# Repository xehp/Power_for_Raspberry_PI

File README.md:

# Power_for_Raspberry_PI
An UPS and some extras for using a Raspberry PI as web interface GUI in an embedded system.

The UPS and HAT selected need to match

RPi_HAT_isolated_rs232 and SuperCapUps10_rs232 are matching.

Copyright (C) 2021
Henrik Björkman
www.eit.se/hb

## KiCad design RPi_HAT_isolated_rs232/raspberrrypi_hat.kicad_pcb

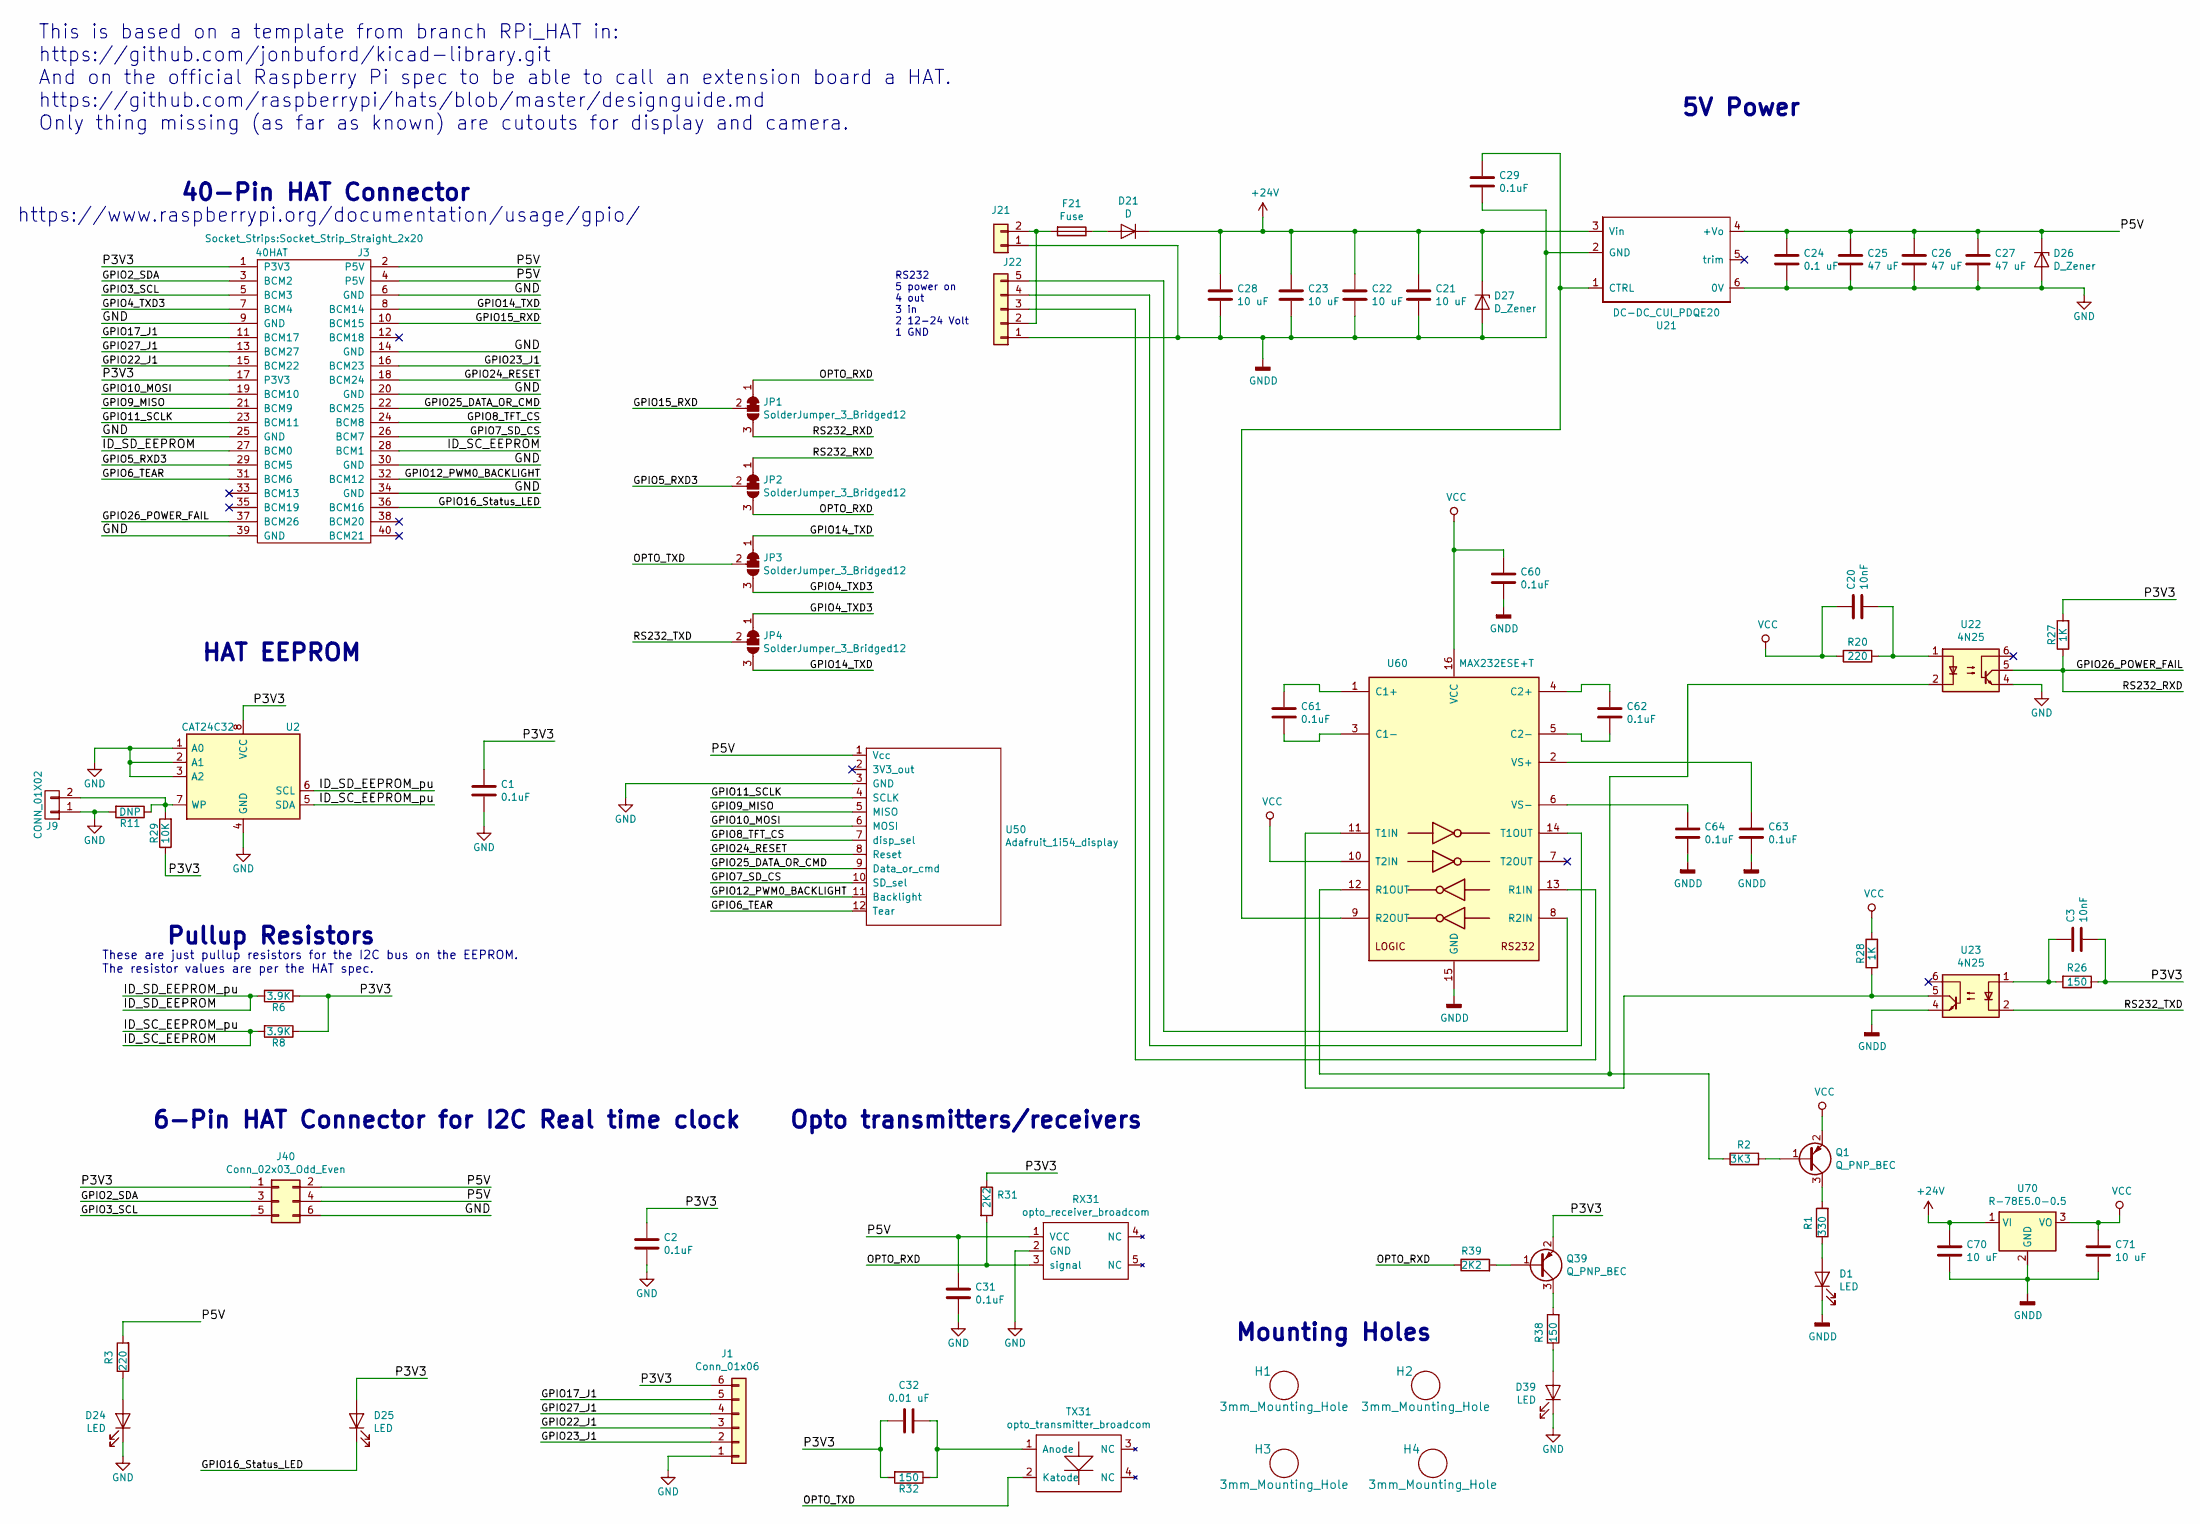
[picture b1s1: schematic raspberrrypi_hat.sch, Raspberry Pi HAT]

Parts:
C1, C2, C31, C60, C61, C62, C63, C64: 0.1uF; C_0805_2012Metric
C3, C20: 10nF; C_0805_2012Metric
C21, C22, C23, C28, C70, C71: 10 uF; C_1206_3216Metric
C24: 0.1 uF; C_0805_2012Metric
C25, C26, C27: 47 uF; C_1206_3216Metric
C29: 0.1uF; C_0805_2012Metric_Pad1.15x1.40mm_HandSolder
C32: 0.01 uF; C_0805_2012Metric
D1, D24, D39: LED; LED_0805_2012Metric
D21: D; D_SMA
D25: LED; LED_D3.0mm
D26: D_Zener; D_SMB
D27: D_Zener; D_A-405_P2.54mm_Vertical_AnodeUp
F21: Fuse; R_Radial_Power_L11.0mm_W7.0mm_P5.00mm
H1, H2, H3, H4: 3mm_Mounting_Hole; NPTH_3mm_ID
J1: Conn_01x06; Molex_KK-254_AE-6410-06A_1x06_P2.54mm_Vertical
J3: 40HAT; Socket_Strip_Straight_2x20
J9: CONN_01X02; PinHeader_1x02_P2.54mm_Vertical
J21: Conn_01x02; connector_TE_Connectivity_2_pin
J22: Conn_01x05; Molex_KK-254_AE-6410-05A_1x05_P2.54mm_Vertical
J40: Conn_02x03_Odd_Even; PinHeader_2x03_P2.54mm_Vertical
JP1, JP2, JP3, JP4: SolderJumper_3_Bridged12; SolderJumper-3_P2.0mm_Open_TrianglePad1.0x1.5mm_NumberLabels
Q1, Q39: Q_PNP_BEC; SOT-23
R1: 330; R_0805_2012Metric_Pad1.15x1.40mm_HandSolder
R2: 3K3; R_0805_2012Metric_Pad1.15x1.40mm_HandSolder
R3: 220; R_0805_2012Metric_Pad1.15x1.40mm_HandSolder
R6, R8: 3.9K; R_0805_2012Metric_Pad1.15x1.40mm_HandSolder; MPN RC0402JR-0722RL
R11: DNP; R_0805_HandSoldering; MPN RC0402JR-0722RL
R20: 220; R_1206_3216Metric; MPN RC0402JR-0722RL
R26: 150; R_0805_2012Metric; MPN RC0402JR-0722RL
R27, R28: 1K; R_0805_2012Metric; MPN RC0402JR-0722RL
R29: 10K; R_0805_2012Metric; MPN RC0402JR-0722RL
R31, R39: 2K2; R_0805_2012Metric_Pad1.15x1.40mm_HandSolder
R32: 150; R_0805_2012Metric_Pad1.15x1.40mm_HandSolder; MPN RC0402JR-0722RL
R38: 150; R_0805_2012Metric_Pad1.15x1.40mm_HandSolder
RX31: opto_receiver_broadcom; opto_receiver_broadwell
TX31: opto_transmitter_broadcom; opto_transmitter_broadwell
U2: CAT24C32; SOIC-8_3.9x4.9mm_Pitch1.27mm
U21: DC-DC_CUI_PDQE20; DC-DC_CUI_PDQE20-D
U22, U23: 4N25; DIP-6_W7.62mm
U50: Adafruit_1i54_display
U60: MAX232ESE+T; SOIC-16_3.9x9.9mm_P1.27mm
U70: R-78E5.0-0.5; DC-DC-Recom-R78

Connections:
+24V: C21.1, C22.1, C23.1, C28.1, C70.1, D21.1 (K), D27.1 (K), U21.3 (Vin), U70.1 (VI)
/GPIO2_SDA: J3.3 (BCM2), J40.3
/GPIO3_SCL: J3.5 (BCM3), J40.5
/GPIO4_TXD3: J3.7 (BCM4), JP3.3 (B), JP4.1 (A)
/GPIO5_RXD3: J3.29 (BCM5), JP2.2 (C)
/GPIO7_SD_CS: J3.26 (BCM7), U50.10 (SD_sel)
/GPIO8_TFT_CS: J3.24 (BCM8), U50.7 (disp_sel)
/GPIO9_MISO: J3.21 (BCM9), U50.5 (MISO)
/GPIO10_MOSI: J3.19 (BCM10), U50.6 (MOSI)
/GPIO11_SCLK: J3.23 (BCM11), U50.4 (SCLK)
/GPIO12_PWM0_BACKLIGHT: J3.32 (BCM12), U50.11 (Backlight)
/GPIO14_TXD: J3.8 (BCM14), JP3.1 (A), JP4.3 (B)
/GPIO15_RXD: J3.10 (BCM15), JP1.2 (C)
/GPIO16_Status_LED: D25.1 (K), J3.36 (BCM16)
/GPIO17_J1: J1.5, J3.11 (BCM17)
/GPIO22_J1: J1.3, J3.15 (BCM22)
/GPIO23_J1: J1.2, J3.16 (BCM23)
/GPIO24_RESET: J3.18 (BCM24), U50.8 (Reset)
/GPIO25_DATA_OR_CMD: J3.22 (BCM25), U50.9 (Data_or_cmd)
/GPIO26_POWER_FAIL: J3.37 (BCM26), JP1.3 (B), JP2.1 (A), R27.1, U22.5
/GPIO27_J1: J1.4, J3.13 (BCM27)
/ID_SC_EEPROM: J3.28 (BCM1), R8.2, U2.5 (SDA)
/ID_SD_EEPROM: J3.27 (BCM0), R6.2, U2.6 (SCL)
/OPTO_RXD: JP1.1 (A), JP2.3 (B), R31.2, R39.1, RX31.3 (signal)
/OPTO_TXD: JP3.2 (C), TX31.2 (Katode)
/P3V3: C1.1, C2.1, C3.2, C32.2, D25.2 (A), J1.6, J3.1 (P3V3), J3.17 (P3V3), J40.1, Q39.2 (E), R6.1, R8.1, R26.1, R27.2, R29.1, R31.1, R32.2, U2.8 (VCC)
/P5V: C24.1, C25.1, C26.1, C27.1, C31.1, D26.1 (K), J3.2 (P5V), J3.4 (P5V), J40.2, J40.4, R3.2, RX31.1 (VCC), U21.4 (+Vo), U50.1 (Vcc)
/RS232_TXD: JP4.2 (C), U23.2
GND: C1.2, C2.2, C24.2, C25.2, C26.2, C27.2, C31.2, D24.1 (K), D26.2 (A), D39.1 (K), J1.1, J3.6 (GND), J3.9 (GND), J3.14 (GND), J3.20 (GND), J3.25 (GND), J3.30 (GND), J3.34 (GND), J3.39 (GND), J9.1, J40.6, R11.2, RX31.2 (GND), U2.1 (A0), U2.2 (A1), U2.3 (A2), U2.4 (GND), U21.6 (0V), U22.4, U50.3 (GND)
GNDD: C21.2, C22.2, C23.2, C28.2, C29.2, C60.2, C63.2, C64.2, C70.2, C71.2, D1.1 (K), D27.2 (A), J21.1, J22.1, U21.2 (GND), U23.4, U60.15 (GND), U70.2 (GND)
unnamed: C3.1, R26.2, U23.1
unnamed: C20.2, R20.1, U22.1
unnamed: C29.1, U21.1 (CTRL), U60.9 (R2OUT)
unnamed: C32.1, R32.1, TX31.1 (Anode)
unnamed: C61.1, U60.1 (C1+)
unnamed: C61.2, U60.3 (C1-)
unnamed: C62.1, U60.4 (C2+)
unnamed: C62.2, U60.5 (C2-)
unnamed: C63.1, U60.2 (VS+)
unnamed: C64.1, U60.6 (VS-)
unnamed: D1.2 (A), R1.1
unnamed: D21.2 (A), F21.1
unnamed: D24.2 (A), R3.1
unnamed: D39.2 (A), R38.1
unnamed: F21.2, J21.2, J22.2
unnamed: J9.2, R11.1, R29.2, U2.7 (WP)
unnamed: J22.3, U60.13 (R1IN)
unnamed: J22.4, U60.14 (T1OUT)
unnamed: J22.5, U60.8 (R2IN)
unnamed: Q1.1 (B), R2.2
unnamed: Q1.3 (C), R1.2
unnamed: Q39.1 (B), R39.2
unnamed: Q39.3 (C), R38.2
unnamed: R2.1, U22.2, U60.12 (R1OUT)
unnamed: R28.1, U23.5, U60.11 (T1IN)
VCC: C20.1, C60.1, C71.1, Q1.2 (E), R20.2, R28.2, U60.10 (T2IN), U60.16 (VCC), U70.3 (VO)

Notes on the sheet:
Pullup Resistors
HAT EEPROM
Mounting Holes
40-Pin HAT Connector
These are just pullup resistors for the I2C bus on the EEPROM. The resistor values are per the HAT spec.
This is based on a template from branch RPi_HAT in: https://github.com/jonbuford/kicad-library.git And on the official Raspberry Pi spec to be able to call an extension board a HAT. https://github.com/raspberrypi/hats/blob/master/designguide.md Only thing missing (as far as known) are cutouts for d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
Opto transmitters/receivers
6-Pin HAT Connector for I2C Real time clock
https://www.raspberrypi.org/documentation/usage/gpio/
5V Power
RS232 5 power on 4 out 3 in 2 12-24 Volt 1 GND

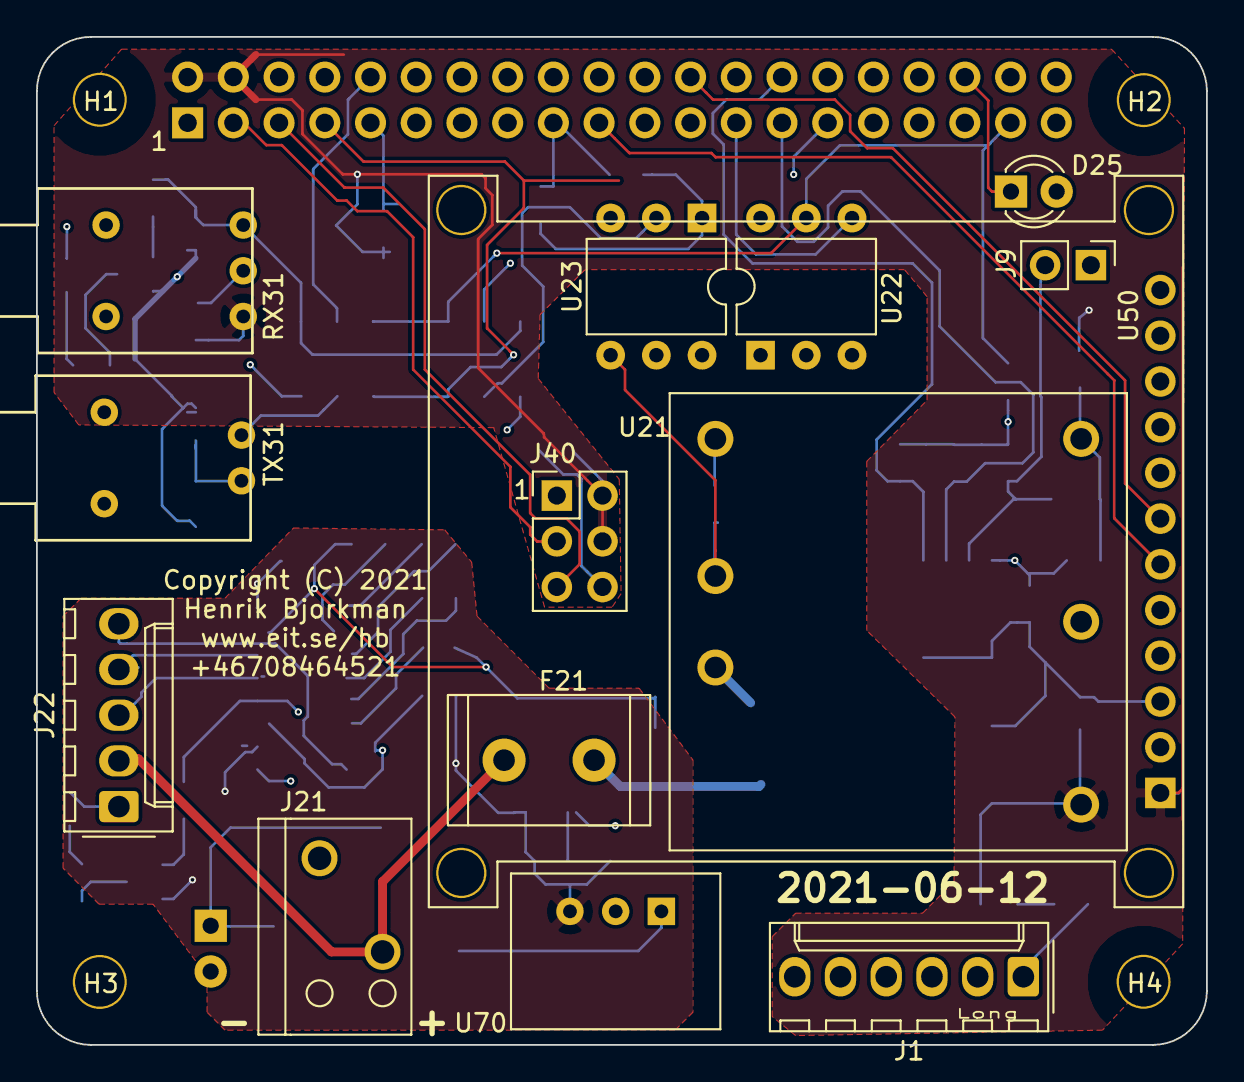
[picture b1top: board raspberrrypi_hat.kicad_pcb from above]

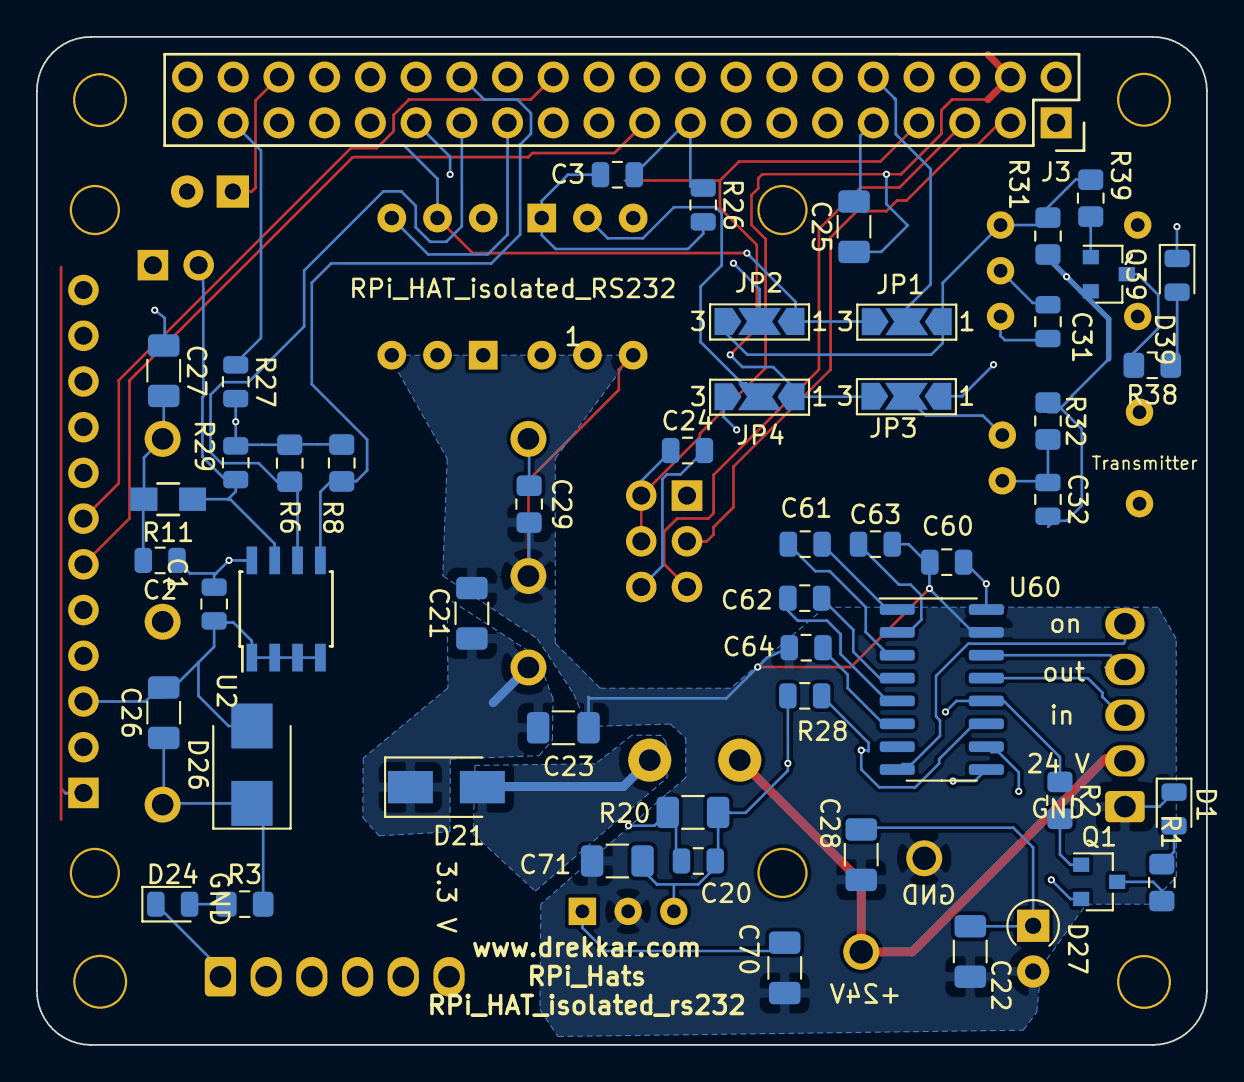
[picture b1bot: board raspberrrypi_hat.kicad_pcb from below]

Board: 4 copper layers, 65.0 x 56.0 mm, 70 parts (52 on the bottom side), 56 nets.

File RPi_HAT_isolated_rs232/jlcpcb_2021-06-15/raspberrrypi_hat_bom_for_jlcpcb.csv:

Comment,Designator,Footprint,LCSC
"10nF","C3,C20","Capacitor_SMD:C_0805_2012Metric",""
"0.1 uF","C24","Capacitor_SMD:C_0805_2012Metric",""
"47 uF","C25,C26,C27","Capacitor_SMD:C_1206_3216Metric",""
"0.1uF","C29","Capacitor_SMD:C_0805_2012Metric_Pad1.15x1.40mm_HandSolder",""
"0.1uF","C1,C2,C31,C60,C61,C62,C63,C64","Capacitor_SMD:C_0805_2012Metric",""
"0.01 uF","C32","Capacitor_SMD:C_0805_2012Metric",""
"10 uF","C21,C22,C23,C28,C70,C71","Capacitor_SMD:C_1206_3216Metric",""
"LED","D1,D24,D39","LED_SMD:LED_0805_2012Metric",""
"D","D21","Diode_SMD:D_SMA",""
"LED","D25","LED_THT:LED_D3.0mm",""
"D_Zener","D26","Diode_SMD:D_SMB",""
"D_Zener","D27","Diode_THT:D_A-405_P2.54mm_Vertical_AnodeUp",""
"Fuse","F21","Resistor_THT:R_Radial_Power_L11.0mm_W7.0mm_P5.00mm",""
"3mm_Mounting_Hole","H1,H2,H3,H4","project_footprints:NPTH_3mm_ID",""
"Conn_01x06","J1","Connector_Molex:Molex_KK-254_AE-6410-06A_1x06_P2.54mm_Vertical",""
"Conn_01x02","J21","eit_footprints:connector_TE_Connectivity_2_pin",""
"Conn_01x05","J22","Connector_Molex:Molex_KK-254_AE-6410-05A_1x05_P2.54mm_Vertical",""
"40HAT","J3","Socket_Strips:Socket_Strip_Straight_2x20",""
"Conn_02x03_Odd_Even","J40","Connector_PinHeader_2.54mm:PinHeader_2x03_P2.54mm_Vertical",""
"CONN_01X02","J9","Connector_PinHeader_2.54mm:PinHeader_1x02_P2.54mm_Vertical",""
"SolderJumper_3_Bridged12","JP1,JP2,JP3,JP4","Jumper:SolderJumper-3_P2.0mm_Open_TrianglePad1.0x1.5mm_NumberLabels",""
"Q_PNP_BEC","Q1,Q39","Package_TO_SOT_SMD:SOT-23",""
"330","R1","Resistor_SMD:R_0805_2012Metric_Pad1.15x1.40mm_HandSolder",""
"DNP","R11","Resistors_SMD:R_0805_HandSoldering",""
"3K3","R2","Resistor_SMD:R_0805_2012Metric_Pad1.15x1.40mm_HandSolder",""
"220","R20","Resistor_SMD:R_1206_3216Metric",""
"150","R26","Resistor_SMD:R_0805_2012Metric",""
"1K","R27,R28","Resistor_SMD:R_0805_2012Metric",""
"10K","R29","Resistor_SMD:R_0805_2012Metric",""
"220","R3","Resistor_SMD:R_0805_2012Metric_Pad1.15x1.40mm_HandSolder",""
"2K2","R31,R39","Resistor_SMD:R_0805_2012Metric_Pad1.15x1.40mm_HandSolder",""
"150","R32,R38","Resistor_SMD:R_0805_2012Metric_Pad1.15x1.40mm_HandSolder",""
"3.9K","R6,R8","Resistor_SMD:R_0805_2012Metric_Pad1.15x1.40mm_HandSolder",""
"opto_receiver_broadcom","RX31","eit_footprints:opto_receiver_broadwell",""
"opto_transmitter_broadcom","TX31","eit_footprints:opto_transmitter_broadwell",""
"CAT24C32","U2","Housings_SOIC:SOIC-8_3.9x4.9mm_Pitch1.27mm",""
"DC-DC_CUI_PDQE20","U21","eit_footprints:DC-DC_CUI_PDQE20-D",""
"4N25","U22,U23","Package_DIP:DIP-6_W7.62mm",""
"Adafruit_1i54_display","U50","eit_footprints:Adafruit_1i54_display",""
"MAX232ESE+T","U60","Package_SO:SOIC-16_3.9x9.9mm_P1.27mm",""
"R-78E5.0-0.5","U70","eit_footprints:DC-DC-Recom-R78",""

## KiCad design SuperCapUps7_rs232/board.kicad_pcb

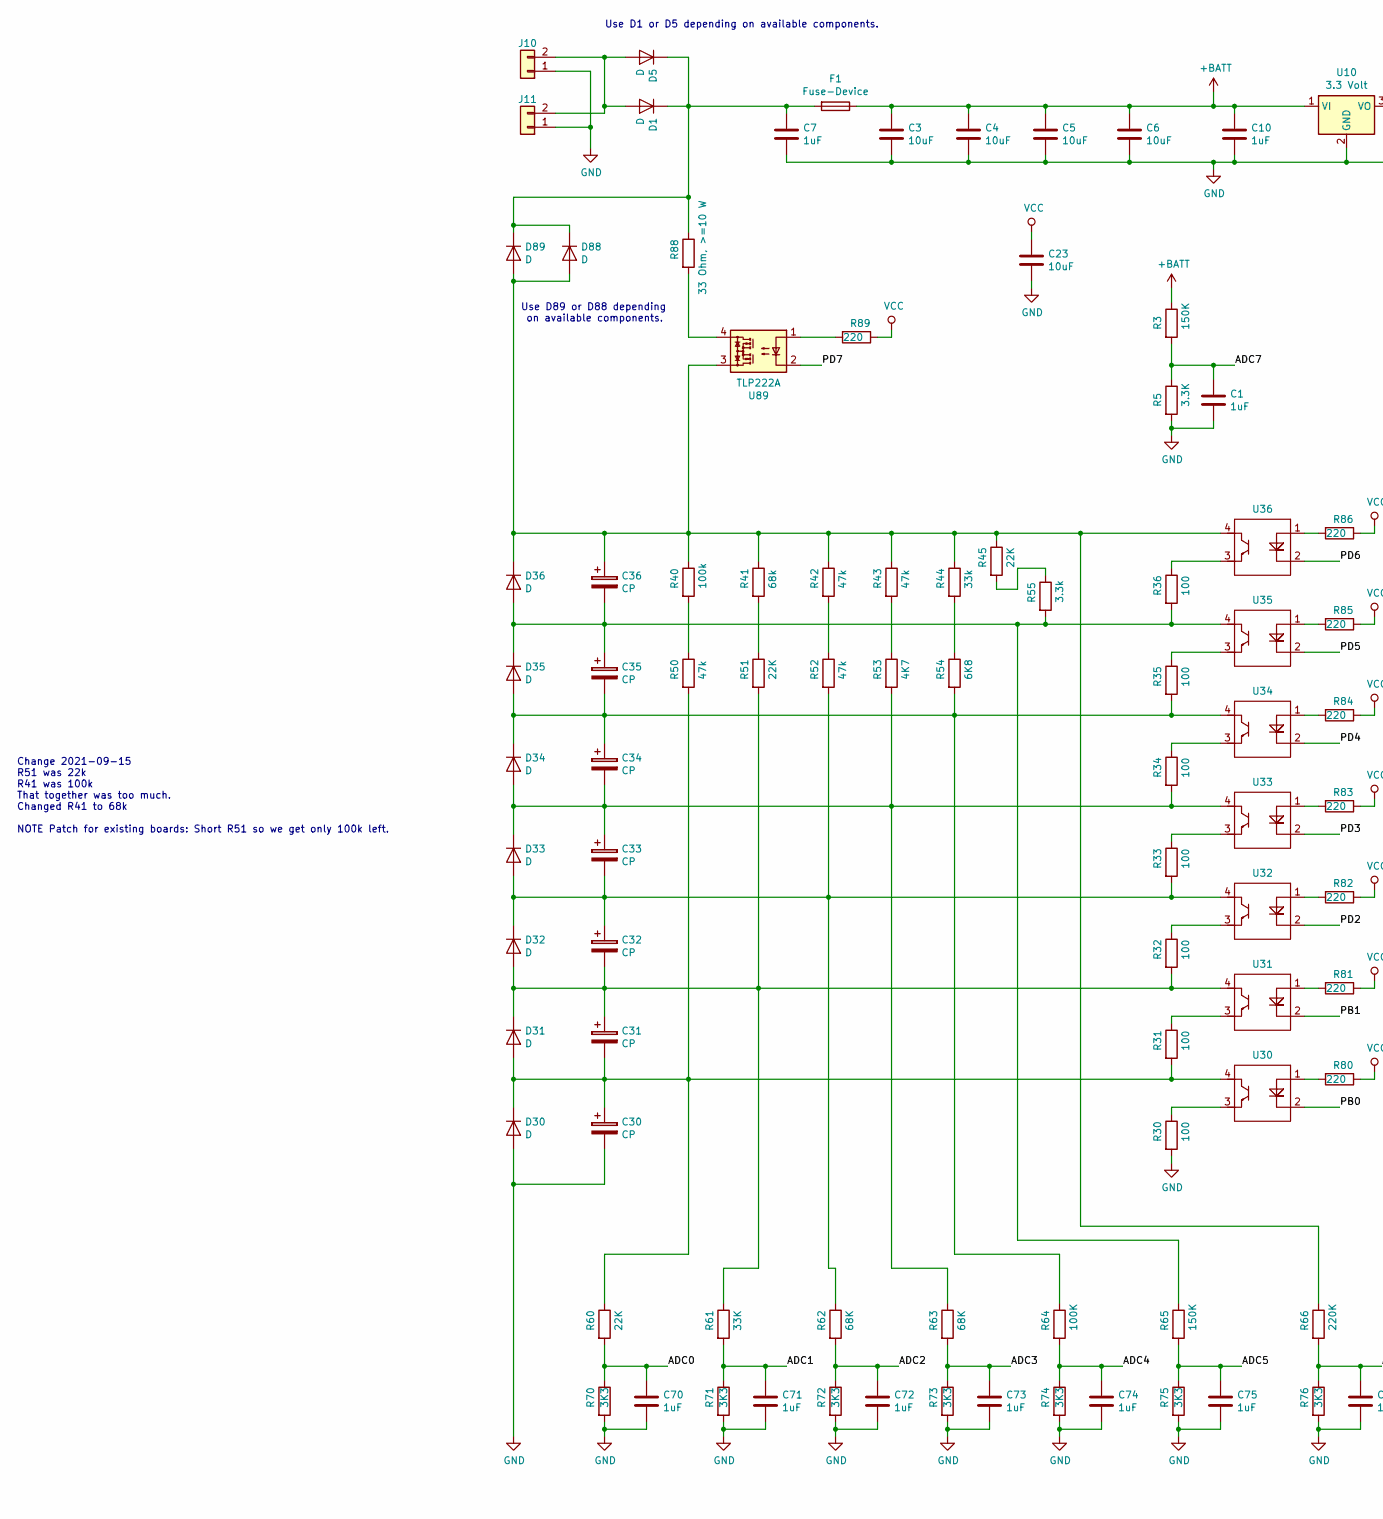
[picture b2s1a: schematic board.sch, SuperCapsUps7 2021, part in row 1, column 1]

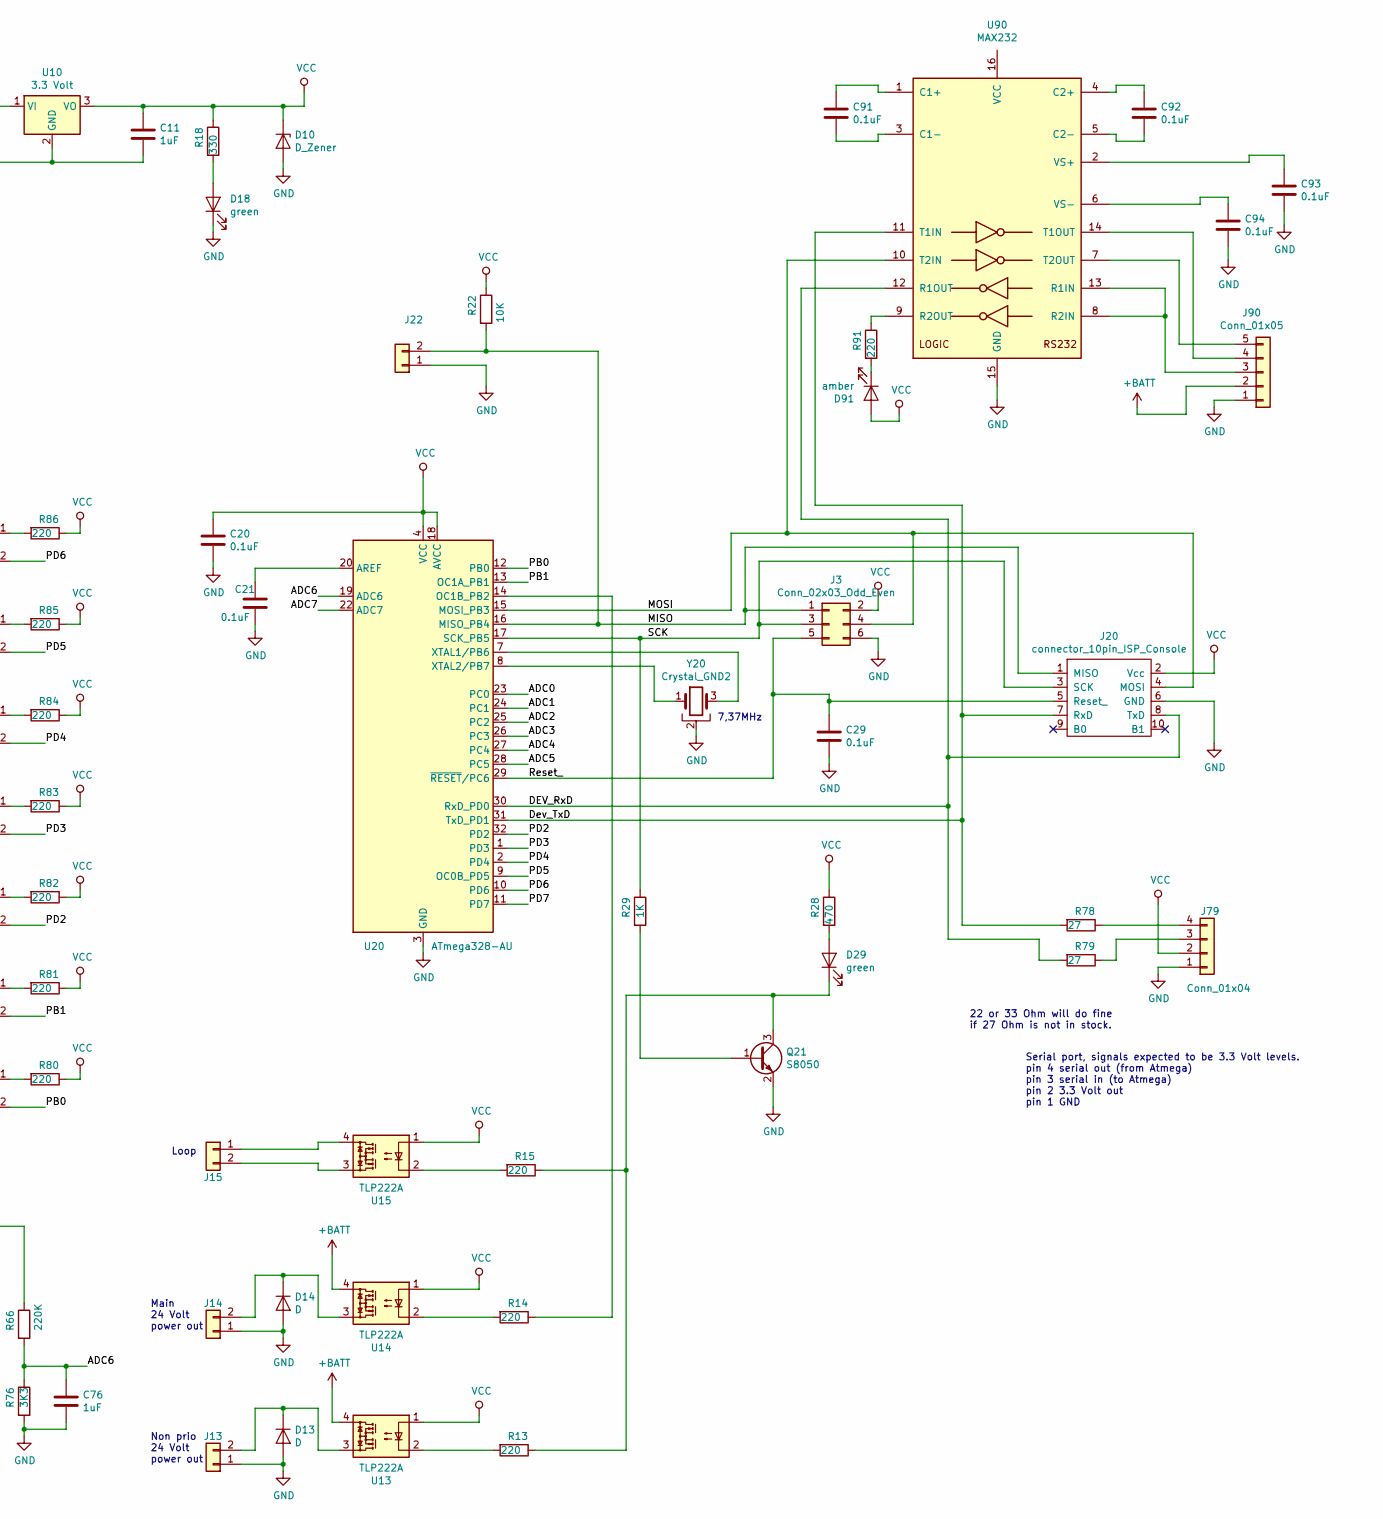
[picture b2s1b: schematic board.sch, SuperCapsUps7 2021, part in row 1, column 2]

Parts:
C1, C7, C10, C11, C70, C71, C72, C73, C74, C75, C76: 1uF; C_0805_2012Metric
C3, C4, C5, C6: 10uF; C_1206_3216Metric
C20, C21, C29, C91, C92, C93, C94: 0.1uF; C_0805_2012Metric
C23: 10uF; C_0805_2012Metric
C30, C31, C32, C33, C34, C35, C36: CP; CP_Radial_D18.0mm_P7.50mm
D1, D89: D; D_SMC
D5, D13, D14, D30, D31, D32, D33, D34, D35, D36, D88: D; D_SMA
D10: D_Zener; D_SMB
D18, D29: green; LED_0805_2012Metric
D91: amber; LED_0805_2012Metric
F1: Fuse-Device; Varistor_RV_Disc_D9mm_W5.7mm_P5mm
J3: Conn_02x03_Odd_Even; PinHeader_2x03_P2.54mm_Vertical
J10, J11, J13, J14, J15: Conn_01x02; connector_TE_Connectivity_2_pin
J20: connector_10pin_ISP_Console; connector_10pin_TC2050-IDC-NL
J22: Conn_01x02; Molex_KK-254_AE-6410-02A_1x02_P2.54mm_Vertical
J79: Conn_01x04; Molex_KK-254_AE-6410-04A_1x04_P2.54mm_Vertical
J90: Conn_01x05; Molex_KK-254_AE-6410-05A_1x05_P2.54mm_Vertical
Q21: S8050; SOT-23
R3, R65: 150K; R_0805_2012Metric
R5: 3.3K; R_0805_2012Metric
R13, R14, R15, R80, R81, R82, R83, R84, R85, R86, R89, R91: 220; R_0805_2012Metric
R18: 330; R_0805_2012Metric
R22: 10K; R_0805_2012Metric
R28: 470; R_0805_2012Metric
R29: 1K; R_0805_2012Metric
R30, R31, R32, R33, R34, R35, R36: 100; R_1206_3216Metric
R40: 100k; R_0805_2012Metric
R41: 68k; R_0805_2012Metric
R42, R43, R50, R52: 47k; R_0805_2012Metric
R44: 33k; R_0805_2012Metric
R45, R51, R60: 22K; R_0805_2012Metric
R53: 4K7; R_0805_2012Metric
R54: 6K8; R_0805_2012Metric
R55: 3.3k; R_0805_2012Metric
R61: 33K; R_0805_2012Metric
R62, R63: 68K; R_0805_2012Metric
R64: 100K; R_0805_2012Metric
R66: 220K; R_0805_2012Metric
R70, R71, R72, R73, R74, R75, R76: 3K3; R_0805_2012Metric
R78, R79: 27; R_0805_2012Metric
R88: 33 Ohm, >=10 W; TO-220-2_with_heatsink_V8508B
U10: 3.3 Volt; DC-DC-Recom-R78
U13, U14, U15, U89: TLP222A; DIP-4_W7.62mm
U20: ATmega328-AU; TQFP-32_7x7mm_P0.8mm
U30, U31, U32, U33, U34, U35, U36: opto_coupler_EL357N(B)(TA)-G; SOP-4_4.1x4.4x2.54P
U90: MAX232; SOIC-16_3.9x9.9mm_P1.27mm
Y20: Crystal_GND2; Resonator-3Pin_W7.0mm_H2.5mm

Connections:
+BATT: C3.1, C4.1, C5.1, C6.1, C10.1, F1.1, J90.2, R3.1, U10.1 (VI), U13.4, U14.4
/ADC0: C70.1, R60.2, R70.1, U20.23 (PC0)
/ADC1: C71.1, R61.2, R71.1, U20.24 (PC1)
/ADC2: C72.1, R62.2, R72.1, U20.25 (PC2)
/ADC3: C73.1, R63.2, R73.1, U20.26 (PC3)
/ADC4: C74.1, R64.2, R74.1, U20.27 (PC4)
/ADC5: C75.1, R65.2, R75.1, U20.28 (PC5)
/ADC6: C76.1, R66.2, R76.1, U20.19 (ADC6)
/ADC7: C1.1, R3.2, R5.1, U20.22 (ADC7)
/DEV_RxD: J20.8 (TxD), R79.2, U20.30 (RxD_PD0), U90.12 (R1OUT)
/Dev_TxD: J20.7 (RxD), R78.2, U20.31 (TxD_PD1), U90.11 (T1IN)
/MISO: J3.1, J20.1 (MISO), J22.2, R22.2, U20.16 (MISO_PB4)
/MOSI: J3.4, J20.4 (MOSI), U20.15 (MOSI_PB3), U90.10 (T2IN)
/PB0: U20.12 (PB0), U30.2
/PB1: U20.13 (OC1A_PB1), U31.2
/PD2: U20.32 (PD2), U32.2
/PD3: U20.1 (PD3), U33.2
/PD4: U20.2 (PD4), U34.2
/PD5: U20.9 (OC0B_PD5), U35.2
/PD6: U20.10 (PD6), U36.2
/PD7: U20.11 (PD7), U89.2
/Reset_: C29.1, J3.5, J20.5 (Reset_), U20.29 (~RESET~/PC6)
/SCK: J3.3, J20.3 (SCK), R29.1, U20.17 (SCK_PB5)
GND: C1.2, C3.2, C4.2, C5.2, C6.2, C7.2, C10.2, C11.2, C20.2, C21.2, C23.2, C29.2, C30.2, C70.2, C71.2, C72.2, C73.2, C74.2, C75.2, C76.2, C93.2, C94.2, D10.2 (A), D13.2 (A), D14.2 (A), D18.1 (K), D30.2 (A), J3.6, J10.1, J11.1, J13.1, J14.1, J20.6 (GND), J22.1, J79.1, J90.1, Q21.2 (E), R5.2, R30.2, R70.2, R71.2, R72.2, R73.2, R74.2, R75.2, R76.2, U10.2 (GND), U20.3 (GND), U20.5 (GND), U20.21 (GND), U90.15 (GND), Y20.2
unnamed: C7.1, D1.1 (K), D5.1 (K), D88.1 (K), D89.1 (K), F1.2, R88.1
unnamed: C21.1, U20.20 (AREF)
unnamed: C30.1, C31.2, D30.1 (K), D31.2 (A), R31.2, R50.2, R60.1, U30.4
unnamed: C31.1, C32.2, D31.1 (K), D32.2 (A), R32.2, R51.2, R61.1, U31.4
unnamed: C32.1, C33.2, D32.1 (K), D33.2 (A), R33.2, R52.2, R62.1, U32.4
unnamed: C33.1, C34.2, D33.1 (K), D34.2 (A), R34.2, R53.2, R63.1, U33.4
unnamed: C34.1, C35.2, D34.1 (K), D35.2 (A), R35.2, R54.2, R64.1, U34.4
unnamed: C35.1, C36.2, D35.1 (K), D36.2 (A), R36.2, R55.2, R65.1, U35.4
unnamed: C36.1, D36.1 (K), D88.2 (A), D89.2 (A), R40.1, R41.1, R42.1, R43.1, R44.1, R45.1, R66.1, U36.4, U89.3
unnamed: C91.1, U90.1 (C1+)
unnamed: C91.2, U90.3 (C1-)
unnamed: C92.1, U90.4 (C2+)
unnamed: C92.2, U90.5 (C2-)
unnamed: C93.1, U90.2 (VS+)
unnamed: C94.1, U90.6 (VS-)
unnamed: D1.2 (A), D5.2 (A), J10.2, J11.2
unnamed: D13.1 (K), J13.2, U13.3
unnamed: D14.1 (K), J14.2, U14.3
unnamed: D18.2 (A), R18.2
unnamed: D29.1 (K), Q21.3 (C), R13.1, R15.1
unnamed: D29.2 (A), R28.2
unnamed: D91.1 (K), R91.2
unnamed: J15.1, U15.4
unnamed: J15.2, U15.3
unnamed: J79.3, R79.1
unnamed: J79.4, R78.1
unnamed: J90.3, U90.8 (R2IN), U90.13 (R1IN)
unnamed: J90.4, U90.14 (T1OUT)
unnamed: J90.5, U90.7 (T2OUT)
unnamed: Q21.1 (B), R29.2
unnamed: R13.2, U13.2
unnamed: R14.1, U20.14 (OC1B_PB2)
unnamed: R14.2, U14.2
unnamed: R15.2, U15.2
unnamed: R30.1, U30.3
unnamed: R31.1, U31.3
unnamed: R32.1, U32.3
unnamed: R33.1, U33.3
unnamed: R34.1, U34.3
unnamed: R35.1, U35.3
unnamed: R36.1, U36.3
unnamed: R40.2, R50.1
unnamed: R41.2, R51.1
unnamed: R42.2, R52.1
unnamed: R43.2, R53.1
unnamed: R44.2, R54.1
unnamed: R45.2, R55.1
unnamed: R80.2, U30.1
unnamed: R81.2, U31.1
unnamed: R82.2, U32.1
unnamed: R83.2, U33.1
unnamed: R84.2, U34.1
unnamed: R85.2, U35.1
unnamed: R86.2, U36.1
unnamed: R88.2, U89.4
unnamed: R89.2, U89.1
unnamed: R91.1, U90.9 (R2OUT)
unnamed: U20.7 (XTAL1/PB6), Y20.3
unnamed: U20.8 (XTAL2/PB7), Y20.1
VCC: C11.1, C20.1, C23.1, D10.1 (K), D91.2 (A), J3.2, J20.2 (Vcc), J79.2, R18.1, R22.1, R28.1, R80.1, R81.1, R82.1, R83.1, R84.1, R85.1, R86.1, R89.1, U10.3 (VO), U13.1, U14.1, U15.1, U20.4 (VCC), U20.6 (VCC), U20.18 (AVCC)

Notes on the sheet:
7,37MHz
Serial port, signals expected to be 3.3 Volt levels. pin 4 serial out (from Atmega) pin 3 serial in (to Atmega) pin 2 3.3 Volt out pin 1 GND
22 or 33 Ohm will do fine if 27 Ohm is not in stock.
Main 24 Volt power out
Non prio 24 Volt power out
Use D1 or D5 depending on available components.
Use D89 or D88 depending on available components.
Loop
Change 2021-09-15 R51 was 22k R41 was 100k That together was too much. Changed R41 to 68k NOTE Patch for existing boards: Short R51 so we get only 100k left.
